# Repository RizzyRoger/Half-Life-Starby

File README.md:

# This is a flashlight schematic made for a single led.
- Turns on when it becomes dark
- Thats basically it

**This project was super helpful in teaching me the basics of wiring.**

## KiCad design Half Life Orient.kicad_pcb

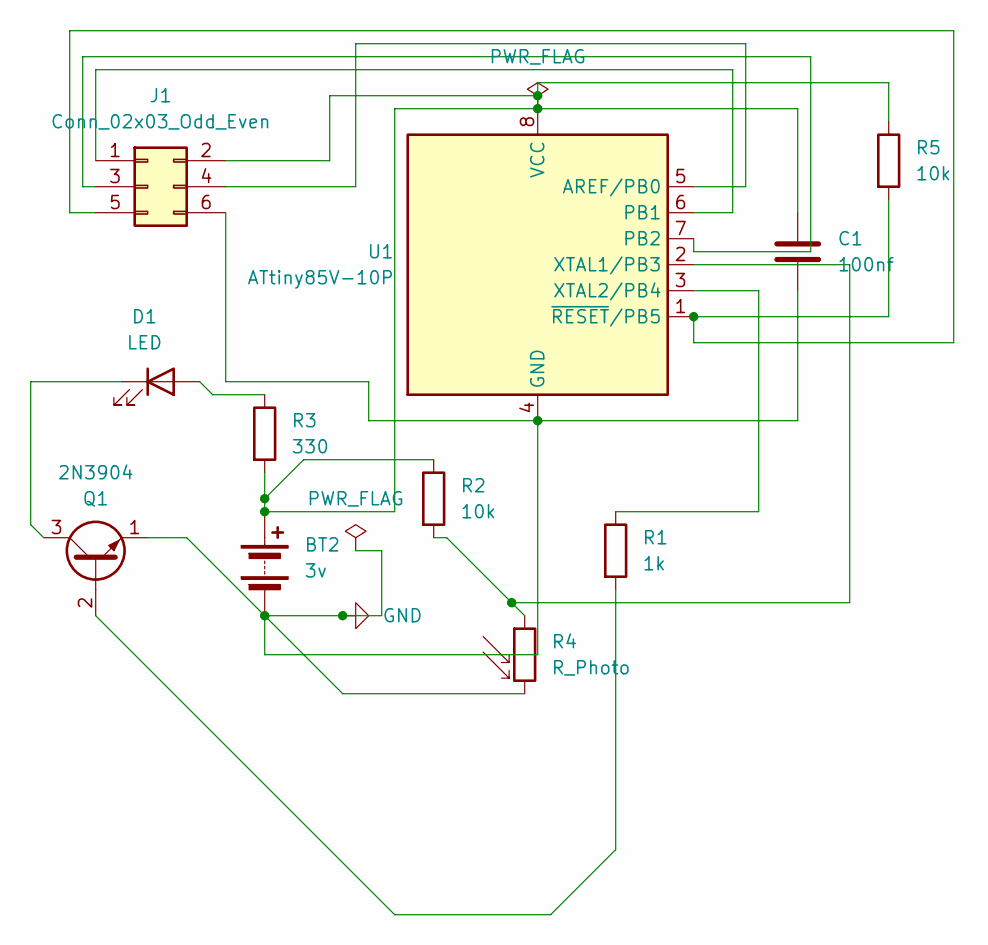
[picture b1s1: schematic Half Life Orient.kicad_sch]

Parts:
BT2: 3v; SolderWire-0.5sqmm_1x02_P4.6mm_D0.9mm_OD2.1mm
C1: 100nf; C_Disc_D5.0mm_W2.5mm_P5.00mm
D1: LED; LED_D5.0mm
J1: Conn_02x03_Odd_Even; PinHeader_2x03_P2.54mm_Vertical
Q1: 2N3904; TO-92_Inline
R1: 1k; R_Axial_DIN0207_L6.3mm_D2.5mm_P7.62mm_Horizontal
R2, R5: 10k; R_Axial_DIN0207_L6.3mm_D2.5mm_P7.62mm_Horizontal
R3: 330; R_Axial_DIN0207_L6.3mm_D2.5mm_P7.62mm_Horizontal
R4: R_Photo; R_LDR_5.0x4.1mm_P3mm_Vertical
U1: ATtiny85V-10P; DIP-8_W7.62mm

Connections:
GND: BT2.2 (-), C1.2, J1.6, Q1.1 (E), R4.2, U1.4 (GND)
unnamed: BT2.1 (+), C1.1, J1.2, R2.1, R3.2, R5.1, U1.8 (VCC)
unnamed: D1.2 (A), R3.1
unnamed: D1.1 (K), Q1.3 (C)
unnamed: J1.1, U1.6 (PB1)
unnamed: J1.3, U1.7 (PB2)
unnamed: J1.4, U1.5 (AREF/PB0)
unnamed: J1.5, R5.2, U1.1 (~RESET/PB5)
unnamed: Q1.2 (B), R1.2
unnamed: R2.2, R4.1, U1.2 (XTAL1/PB3)
unnamed: R1.1, U1.3 (XTAL2/PB4)

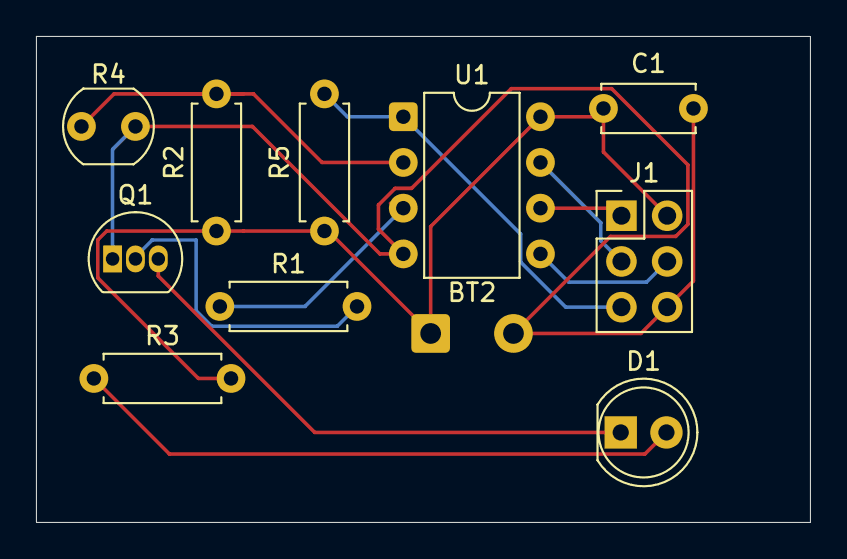
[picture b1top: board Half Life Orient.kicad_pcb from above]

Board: 2 copper layers, 43.0 x 27.0 mm, 11 parts (0 on the bottom side), 11 nets.
